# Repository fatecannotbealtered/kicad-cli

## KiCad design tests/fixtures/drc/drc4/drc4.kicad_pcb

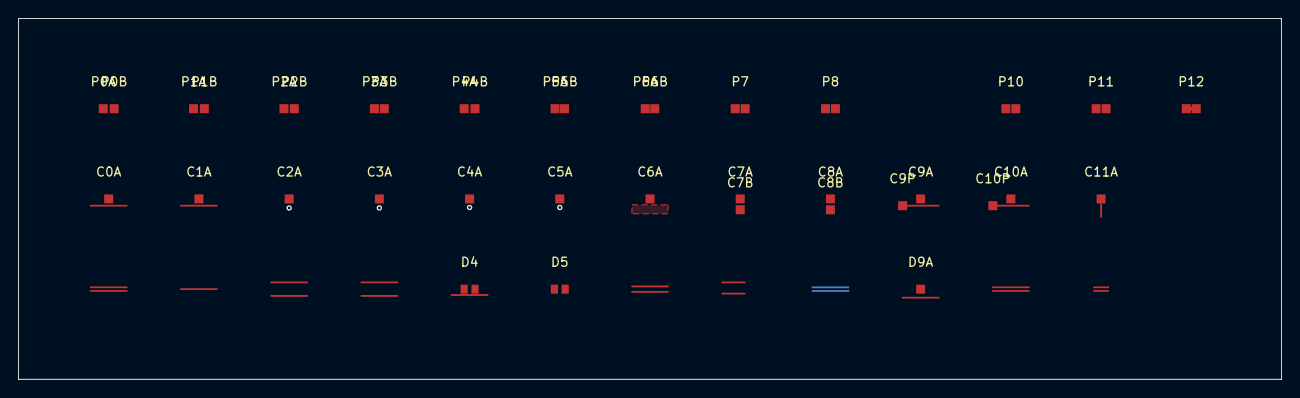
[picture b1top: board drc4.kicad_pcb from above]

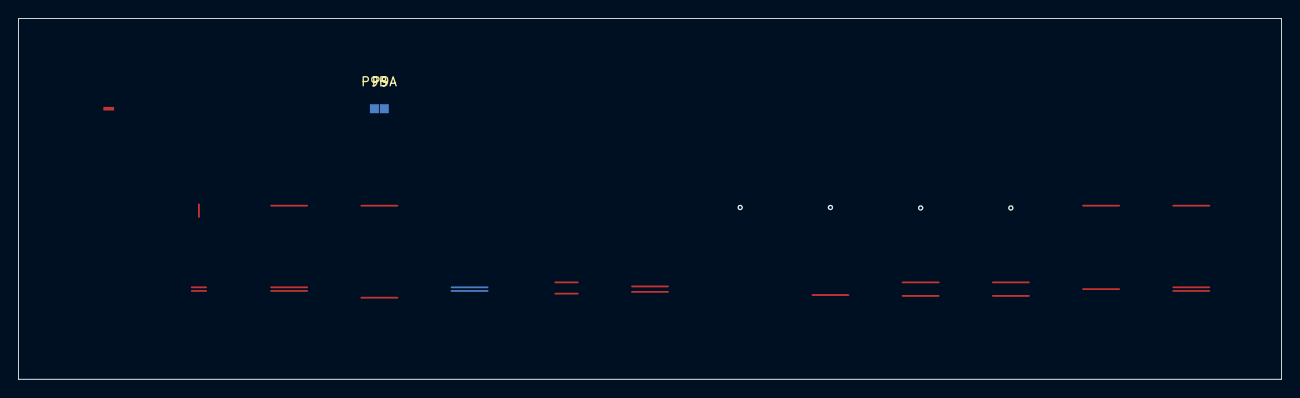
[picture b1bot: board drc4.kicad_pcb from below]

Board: 4 copper layers, 140.0 x 40.0 mm, 40 parts (2 on the bottom side), 2 nets.

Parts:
C0A: C0A
C1A: C1A
C2A: C2A
C3A: C3A
C4A: C4A
C5A: C5A
C6A: C6A
C7A: C7A
C7B: C7B
C8A: C8A
C8B: C8B
C9A: C9A
C9P: C9P
C10A: C10A
C10P: C10P
C11A: C11A
D4: D4
D5: D5
D9A: D9A
P0A: P0A
P0B: P0B
P1A: P1A
P1B: P1B
P2A: P2A
P2B: P2B
P3A: P3A
P3B: P3B
P4A: P4A
P4B: P4B
P5A: P5A
P5B: P5B
P6A: P6A
P6B: P6B
P7: P7
P8: P8
P9A: P9A
P9B: P9B
P10: P10
P11: P11
P12: P12

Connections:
C9a: C9A.1, C9P.1
P5a: P5A.1, P5B.1

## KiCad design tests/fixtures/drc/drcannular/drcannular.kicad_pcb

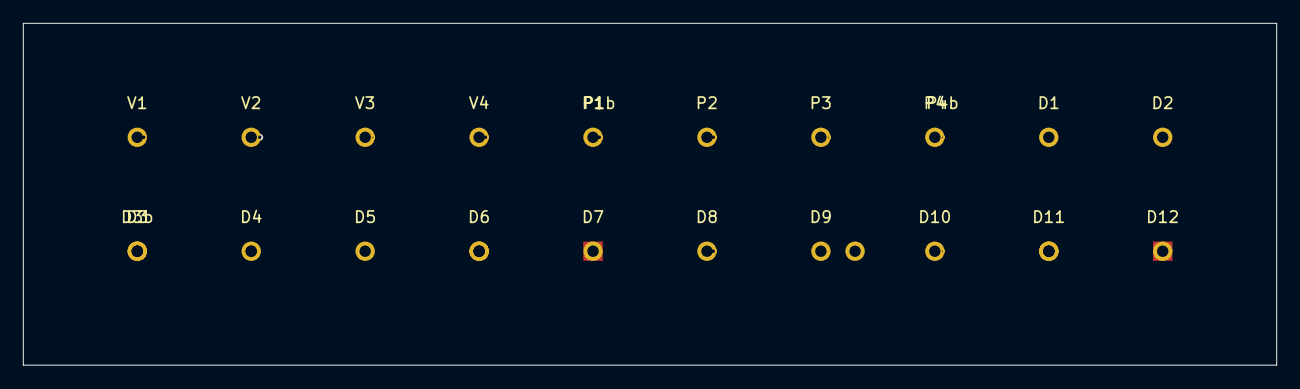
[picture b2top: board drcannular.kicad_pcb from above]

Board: 4 copper layers, 110.0 x 30.0 mm, 23 parts (0 on the bottom side), 8 nets, no tracks yet.

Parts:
D1: D1
D2: D2
D3: D3
D3b: D3b
D4: D4
D5: D5
D6: D6
D7: D7
D8: D8
D9: D9
D10: D10
D11: D11
D12: D12
P1: P1
P1b: P1b
P2: P2
P3: P3
P4: P4
P4b: P4b
V1: V1
V2: V2
V3: V3
V4: V4

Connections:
D3: D3.1, D3b.1
D5: D5.1, D5.2
D6: D6.1, D6.2
D7: D7.1, D7.2
P1: P1.1, P1b.1
P2: P2.1, P2.2
P3: P3.1, P3.2
P4: P4.1, P4b.1
